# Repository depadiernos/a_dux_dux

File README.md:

# A DUX DUX

36 keys, vertical stagger, splayed columns.

Based on Architeuthis Dux with a unique flippable design.

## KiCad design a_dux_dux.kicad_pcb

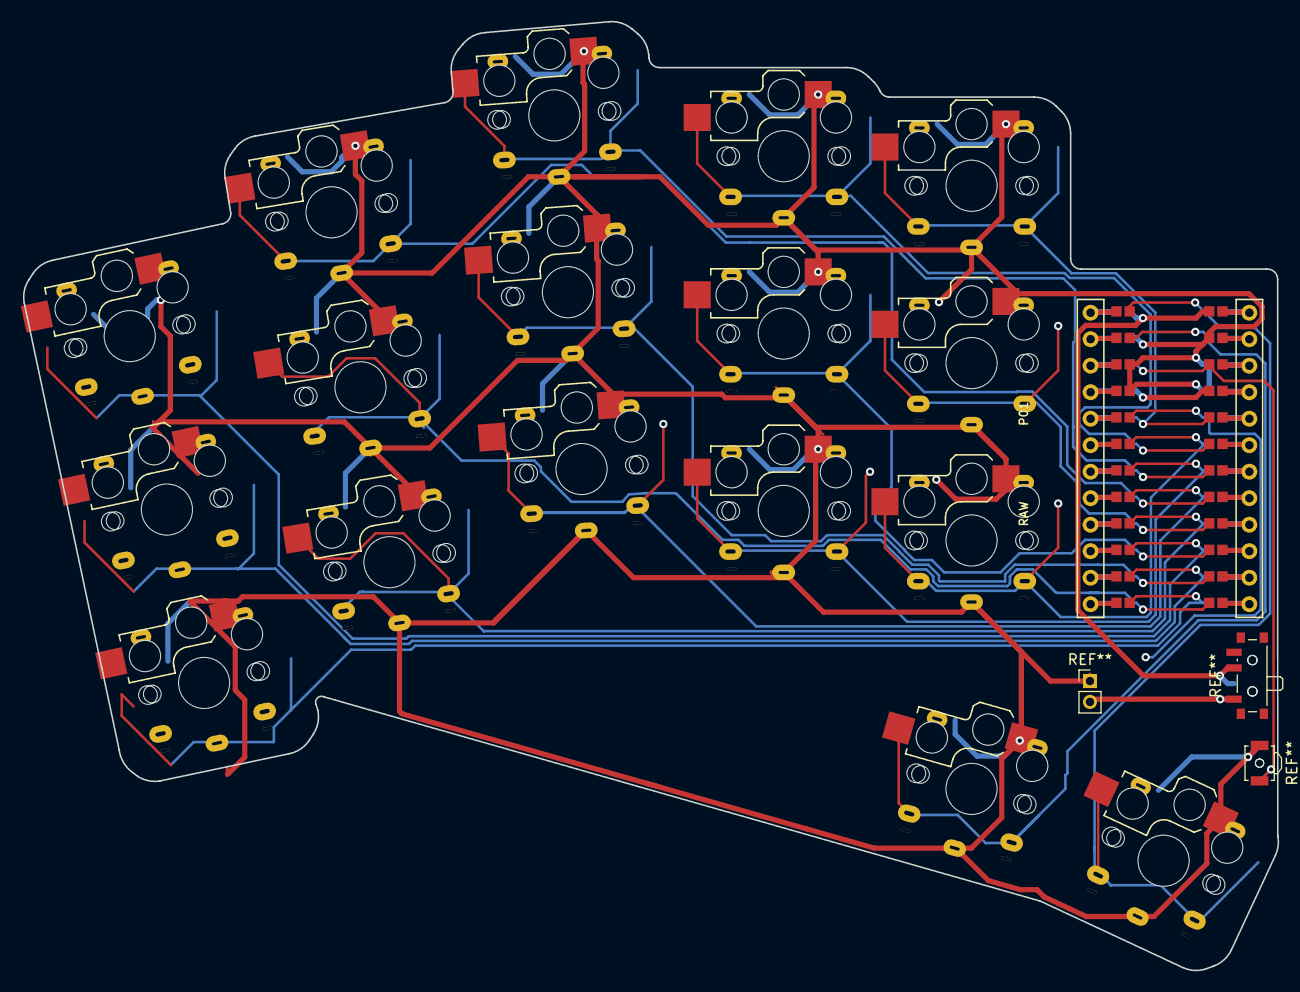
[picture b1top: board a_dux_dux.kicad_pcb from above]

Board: 2 copper layers, 120.3 x 90.9 mm, 18 parts (0 on the bottom side), 18 nets.

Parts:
C1: ProMicro_Jumper
S2, S4, S6, S8, S10, S12, S14, S16, S18, S20, S22, S24, S26, S28, S30, S32, S34: CherryMX_ChocV2_1u_flip

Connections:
GND: C1.2, C1.15, C1.16, S2.2, S4.2, S6.2, S8.2, S10.2, S12.2, S14.2, S16.2, S18.2, S20.2, S22.2, S24.2, S26.2, S28.2, S30.2, S32.2, S34.2
P0: C1.14, S32.1
P1: C1.13, S34.1
P3: C1.18, S26.1
P4: C1.19, S20.1
P5: C1.20, S14.1
P6: C1.21, S8.1
P7: C1.22, S6.1
P8: C1.23, S4.1
P9: C1.24, S2.1
P10: C1.12, S10.1
P14: C1.10, S22.1
P15: C1.9, S28.1
P16: C1.11, S16.1
P18: C1.8, S12.1
P19: C1.7, S18.1
P20: C1.6, S24.1
P21: C1.5, S30.1

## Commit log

2021-11-08 a_dux_dux
2021-11-16 add hotswap support and remove third thumb key
2021-11-16 move board to see if that fixes the phantom hole in jlcpcb
2021-11-16 add hotswap gerbers
2021-11-16 update hotswap gerbers
2021-11-17 less pinky stagger based on initial impressions
2021-11-17 generate gerber for less stagger version
